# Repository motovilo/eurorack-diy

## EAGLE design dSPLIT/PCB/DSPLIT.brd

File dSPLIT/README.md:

# dSPLIT
 5-way digital splitter, x2, x4 divider module

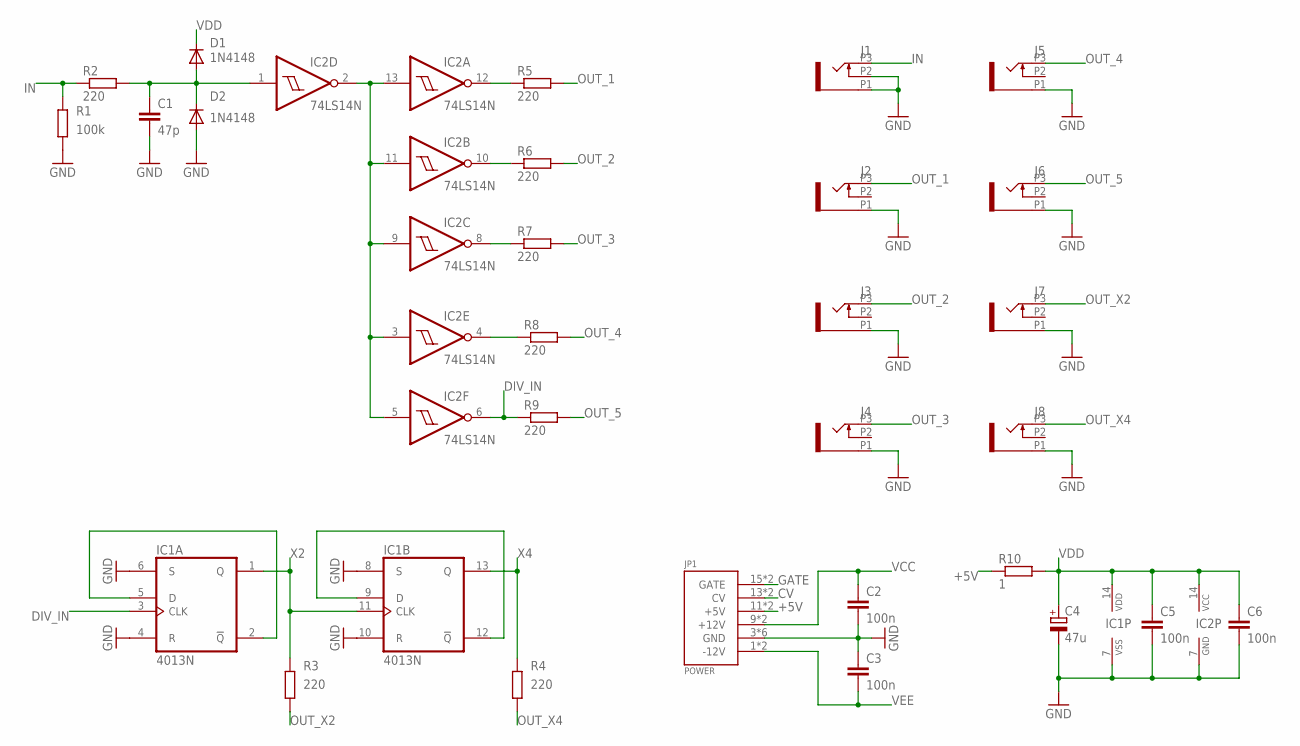
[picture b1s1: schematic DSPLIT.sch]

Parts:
C1: 47p; C050-024X044
C2, C3, C5, C6: 100n; C050-024X044
C4: 47u; E2,5-6
D1, D2: 1N4148; DO35-7
IC1: 4013N; DIL14
IC2: 74LS14N; DIL14
J1, J2, J3, J4, J5, J6, J7, J8: WQP-PJ302M_JACK
JP1: POWER; POWER_16
R1: 100k; 0204/7
R2, R3, R4, R5, R6, R7, R8, R9: 220; 0204/7
R10: 1; 0204/7

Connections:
+5V: JP1.11 (+5V), JP1.12 (+5V), R10.1
CV: JP1.13 (CV), JP1.14 (CV)
DIV_IN: IC1.3 (CLK), IC2.6 (O), R9.1
GATE: JP1.15 (GATE), JP1.16 (GATE)
GND: C1.2, C2.2, C3.1, C4.-, C5.2, C6.2, D2.A, IC1.4 (R), IC1.6 (S), IC1.7 (VSS), IC1.8 (S), IC1.10 (R), IC2.7 (GND), J1.P1 (1), J1.P2 (2), J2.P1 (1), J3.P1 (1), J4.P1 (1), J5.P1 (1), J6.P1 (1), J7.P1 (1), J8.P1 (1), JP1.3 (GND), JP1.4 (GND), JP1.5 (GND), JP1.6 (GND), JP1.7 (GND), JP1.8 (GND), R1.1
IN: J1.P3 (3), R1.2, R2.1
IN_1_: C1.1, D1.A, D2.C, IC2.1 (I), R2.2
unnamed: IC1.2 (!Q), IC1.5 (D)
unnamed: IC2.2 (O), IC2.3 (I), IC2.5 (I), IC2.9 (I), IC2.11 (I), IC2.13 (I)
unnamed: IC1.9 (D), IC1.12 (!Q)
unnamed: IC2.12 (O), R5.1
unnamed: IC2.10 (O), R6.1
unnamed: IC2.8 (O), R7.1
unnamed: IC2.4 (O), R8.1
OUT_1: J2.P3 (3), R5.2
OUT_2: J3.P3 (3), R6.2
OUT_3: J4.P3 (3), R7.2
OUT_4: J5.P3 (3), R8.2
OUT_5: J6.P3 (3), R9.2
OUT_X2: J7.P3 (3), R3.2
OUT_X4: J8.P3 (3), R4.2
VCC: C2.1, JP1.9 (+12V), JP1.10 (+12V)
VDD: C4.+, C5.1, C6.1, D1.C, IC1.14 (VDD), IC2.14 (VCC), R10.2
VEE: C3.2, JP1.1 (-12V), JP1.2 (-12V)
X2: IC1.1 (Q), IC1.11 (CLK), R3.1
X4: IC1.13 (Q), R4.1

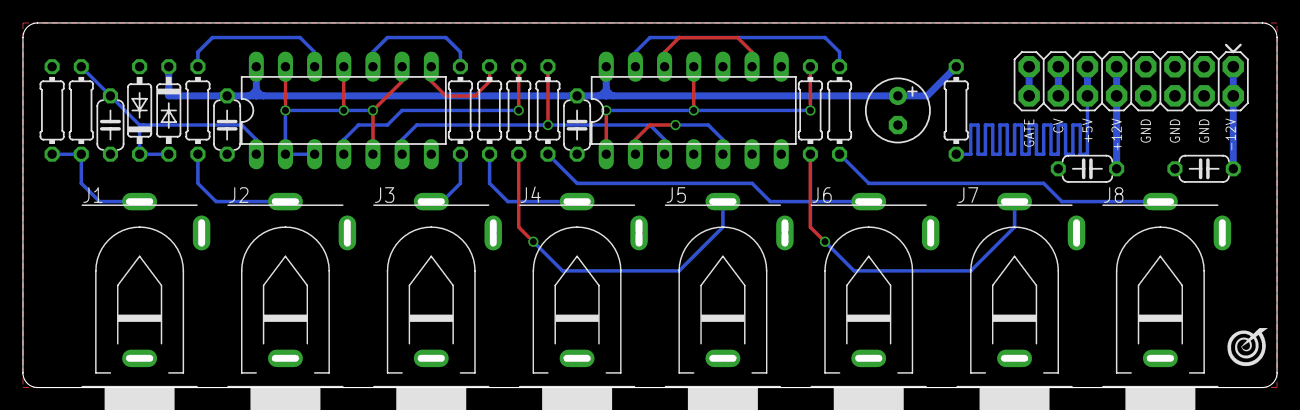
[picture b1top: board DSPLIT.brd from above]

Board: 2 copper layers, 108.6 x 31.1 mm, 31 parts (1 on the bottom side), 26 nets.

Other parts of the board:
U$1: LOGO_SPACE_002
U$2: LOGO_1

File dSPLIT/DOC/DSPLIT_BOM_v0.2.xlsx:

Part | QTY | Value | Device | Package
C1 | 1 | 47p | CAPACITOR CERAMIC | C050-024X044
C2, C3, C5, C6 | 4 | 100n | CAPACITOR CERAMIC | C050-024X044
C4 | 1 | 47u | CAPACITOR ELECTROLYTIC | E2,5-6
D1, D2 | 2 | 1N4148 | DIODE | DO35-7
IC1 | 1 | CD4013N | Dual D FLIP FLOP, set/reset | DIL14
IC2 | 1 | 74LS14N (or CD40106) | Hex schmitt trigger INVERTER | DIL14
J1, J2, J3, J4, J5, J6, J7, J8 | 8 | WQP-PJ302M | MONO JACK 3.5mm with switch angle mount | WQP-PJ302M_JACK
JP1 | 1 | POWER | PIN HEADER 16*2 PITCH=2.54mm | PLD-16 (DS1021-2x8)
R1 | 1 | 100k | RESISTOR METAL FILM 1/4W | 0204/7
R2, R3, R4, R5, R6, R7, R8, R9 | 8 | 220 | RESISTOR METAL FILM 1/4W | 0204/7
R10 | 1 | 1 | RESISTOR METAL FILM 1/4W | 0204/7
IC1, IC2 | 2 | IC SOCKET | IC SOCKET DIL 14 PIN | SCS-14 (DS1009-14AN)
Screw M3 | 2 |  | SCREW M3*6 ROUND CAP | M3*6
Flat Cable 10 PIN | 1 |  | Flat Cable 1.27mm*16 | DS1057-16-30 (FRC-16-30)
FC-16P Connector for flat cable | 2 | IDC-16F | 2.54mm IDC SOCKET 16 pin | IDC-16F (DS1016-16)
dSPLIT PCB v.0.2 | 1
dSPLIT PANEL | 1
NUTS for JACKS | 8

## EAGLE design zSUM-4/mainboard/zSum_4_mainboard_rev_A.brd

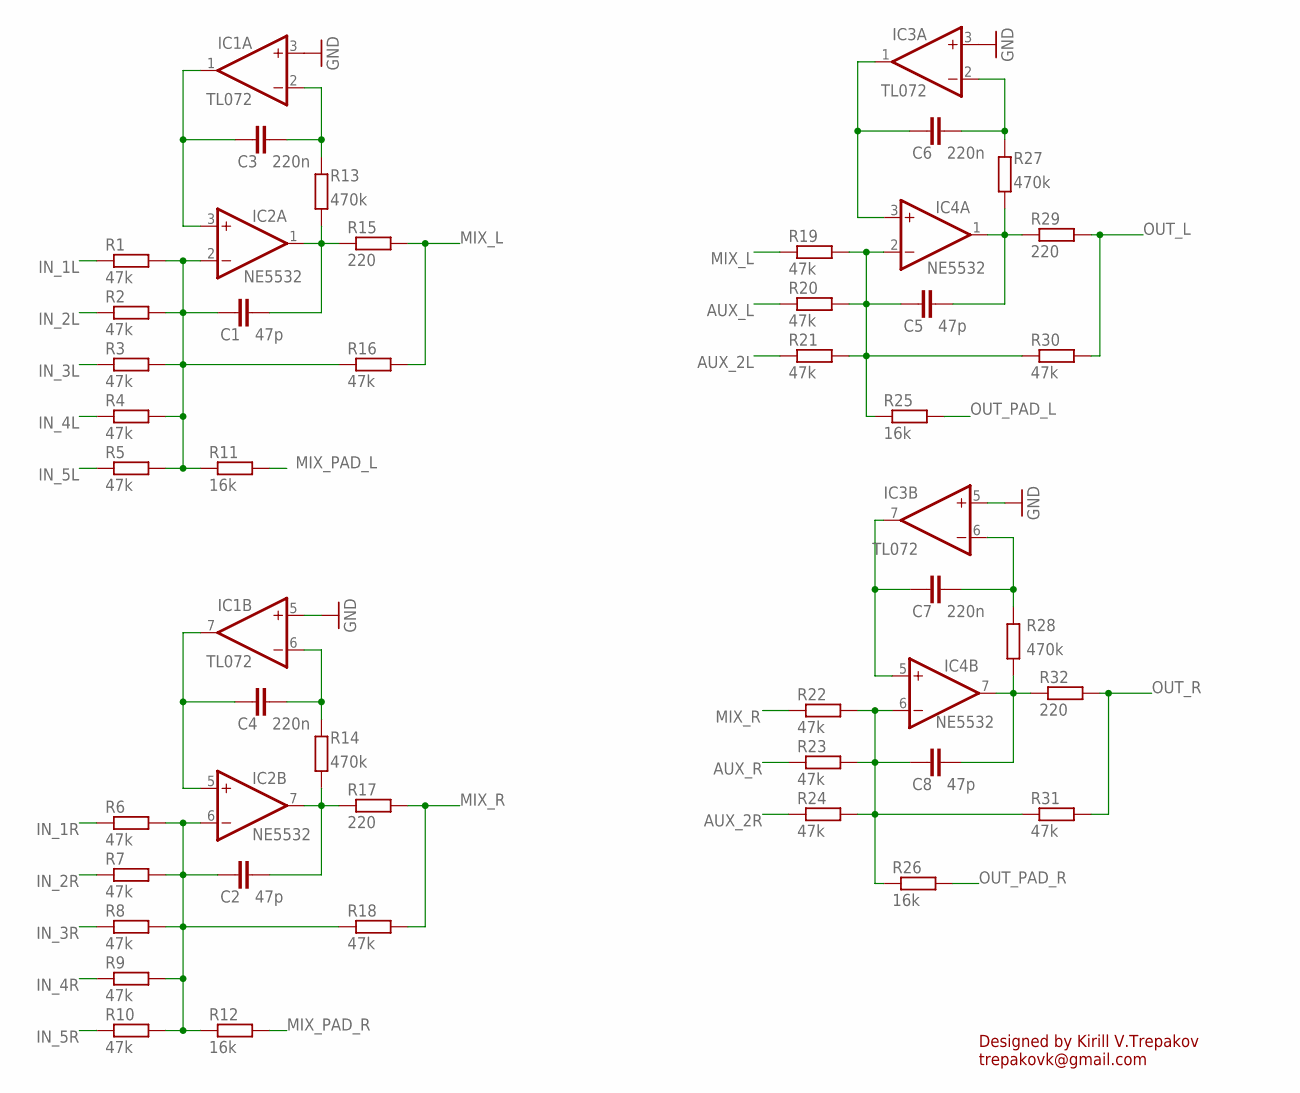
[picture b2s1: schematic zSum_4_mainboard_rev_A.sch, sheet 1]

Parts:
C1, C2, C5, C8: 47p; C025-025X050
C3, C4, C6, C7: 220n; C050-025X075
IC1, IC3: TL072; DIL08
IC2, IC4: NE5532; DIL08
R1, R2, R3, R4, R5, R6, R7, R8, R9, R10, R16, R18, R19, R20, R21, R22, R23, R24, R30, R31: 47k; 0207/7
R11, R12, R25, R26: 16k; 0207/7
R13, R14, R27, R28: 470k; 0207/7
R15, R17, R29, R32: 220; 0207/7

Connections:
AUX_2L: R21.1; also elsewhere on the board
AUX_2R: R24.1; also elsewhere on the board
AUX_L: R20.1; also elsewhere on the board
AUX_R: R23.1; also elsewhere on the board
BIAS_L: C3.2, IC1.1 (OUT), IC2.3 (+IN)
BIAS_L1: C6.2, IC3.1 (OUT), IC4.3 (+IN)
BIAS_R: C4.2, IC1.7 (OUT), IC2.5 (+IN)
BIAS_R1: C7.2, IC3.7 (OUT), IC4.5 (+IN)
GND: IC1.3 (+IN), IC1.5 (+IN), IC3.3 (+IN), IC3.5 (+IN); also elsewhere on the board
IN_1L: R1.1; also elsewhere on the board
IN_1R: R6.1; also elsewhere on the board
IN_2L: R2.1; also elsewhere on the board
IN_2R: R7.1; also elsewhere on the board
IN_3L: R3.1; also elsewhere on the board
IN_3R: R8.1; also elsewhere on the board
IN_4L: R4.1; also elsewhere on the board
IN_4R: R9.1; also elsewhere on the board
IN_5L: R5.1; also elsewhere on the board
IN_5R: R10.1; also elsewhere on the board
MIX_L: R15.2, R16.2, R19.1; also elsewhere on the board
MIX_PAD_L: R11.2; also elsewhere on the board
MIX_PAD_R: R12.2; also elsewhere on the board
MIX_R: R17.2, R18.2, R22.1; also elsewhere on the board
unnamed: C6.1, IC3.2 (-IN), R27.1
unnamed: C7.1, IC3.6 (-IN), R28.1
unnamed: C3.1, IC1.2 (-IN), R13.1
unnamed: C1.1, IC2.1 (OUT), R13.2, R15.1
unnamed: C4.1, IC1.6 (-IN), R14.1
unnamed: C2.1, IC2.7 (OUT), R14.2, R17.1
unnamed: C5.1, IC4.1 (OUT), R27.2, R29.1
unnamed: C8.1, IC4.7 (OUT), R28.2, R32.1
OUT_L: R29.2, R30.2; also elsewhere on the board
OUT_PAD_L: R25.2; also elsewhere on the board
OUT_PAD_R: R26.2; also elsewhere on the board
OUT_R: R31.2, R32.2; also elsewhere on the board
VGND_MIX_L: C1.2, IC2.2 (-IN), R1.2, R2.2, R3.2, R4.2, R5.2, R11.1, R16.1
VGND_MIX_R: C2.2, IC2.6 (-IN), R6.2, R7.2, R8.2, R9.2, R10.2, R12.1, R18.1
VGND_OUT_L: C5.2, IC4.2 (-IN), R19.2, R20.2, R21.2, R25.1, R30.1
VGND_OUT_R: C8.2, IC4.6 (-IN), R22.2, R23.2, R24.2, R26.1, R31.1

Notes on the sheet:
Designed by Kirill V.Trepakov trepakovk@gmail.com

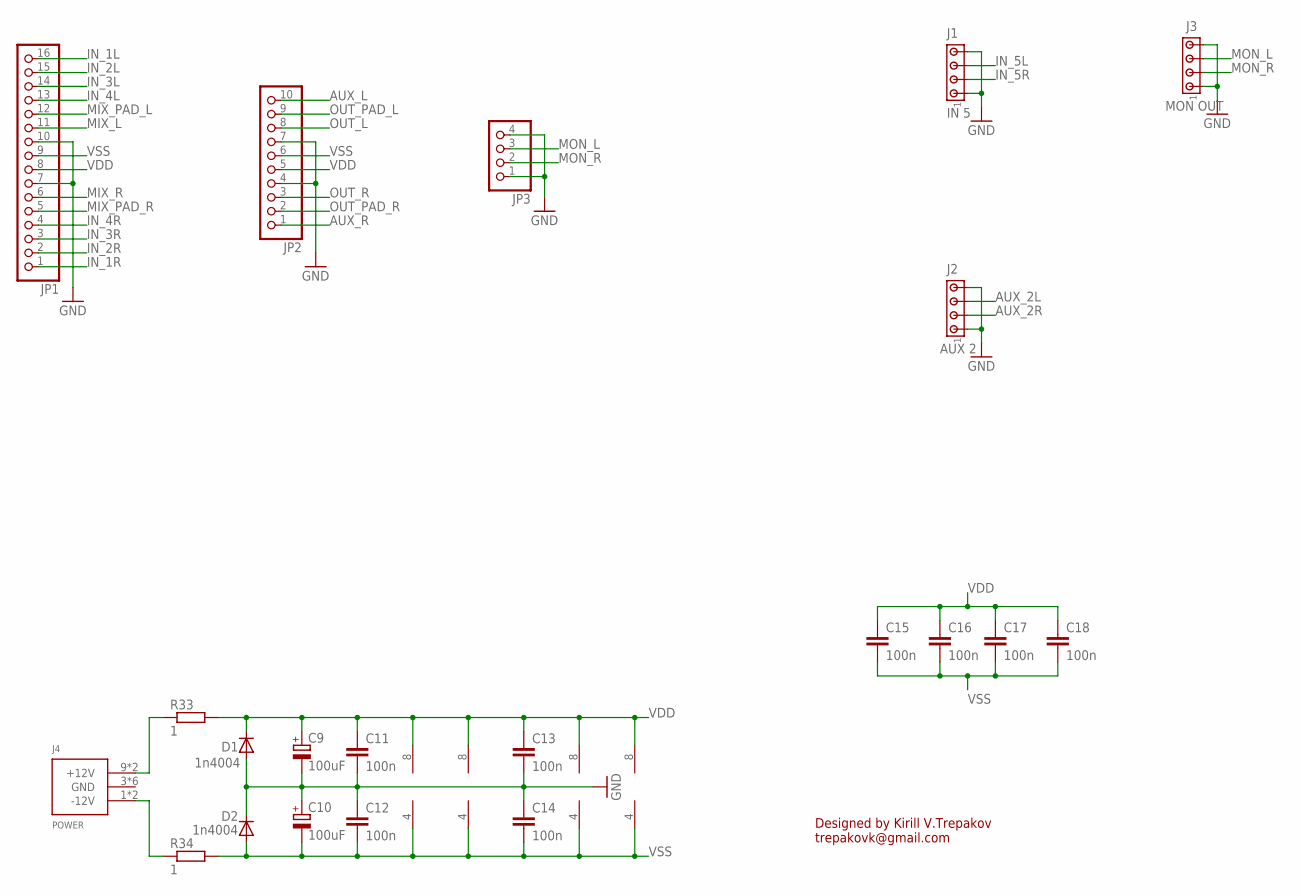
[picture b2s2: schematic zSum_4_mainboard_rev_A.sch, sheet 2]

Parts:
C9, C10: 100uF; E2,5-6
C11, C12, C13, C14: 100n; C050-025X075
C15, C16, C17, C18: 100n; C1206
D1, D2: 1n4004; DO41-7.6
IC1, IC3: TL072; DIL08
IC2, IC4: NE5532; DIL08
J1: IN 5; 10X04MTA
J2: AUX 2; 10X04MTA
J3: MON OUT; 10X04MTA
J4: POWER; POWER_10M
JP1: PINHD-1X16; 1X16_
JP2: PINHD-1X10; 1X10_
JP3: PINHD-1X4; 1X04
R33, R34: 1; 0207/7

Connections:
AUX_2L: J2.3; also elsewhere on the board
AUX_2R: J2.2; also elsewhere on the board
AUX_L: JP2.10; also elsewhere on the board
AUX_R: JP2.1; also elsewhere on the board
GND: C9.-, C10.+, C11.2, C12.1, C13.2, C14.1, D1.A, D2.C, J1.1, J1.4, J2.1, J2.4, J3.1, J3.4, JP1.7, JP1.10, JP2.4, JP2.7, JP3.1, JP3.4; also elsewhere on the board
IN_1L: JP1.16; also elsewhere on the board
IN_1R: JP1.1; also elsewhere on the board
IN_2L: JP1.15; also elsewhere on the board
IN_2R: JP1.2; also elsewhere on the board
IN_3L: JP1.14; also elsewhere on the board
IN_3R: JP1.3; also elsewhere on the board
IN_4L: JP1.13; also elsewhere on the board
IN_4R: JP1.4; also elsewhere on the board
IN_5L: J1.3; also elsewhere on the board
IN_5R: J1.2; also elsewhere on the board
MIX_L: JP1.11; also elsewhere on the board
MIX_PAD_L: JP1.12; also elsewhere on the board
MIX_PAD_R: JP1.5; also elsewhere on the board
MIX_R: JP1.6; also elsewhere on the board
MON_L: J3.3, JP3.3
MON_R: J3.2, JP3.2
unnamed: J4.1 (-12V), J4.2 (-12V), R34.1
unnamed: J4.9 (+12V), J4.10 (+12V), R33.1
OUT_L: JP2.8; also elsewhere on the board
OUT_PAD_L: JP2.9; also elsewhere on the board
OUT_PAD_R: JP2.2; also elsewhere on the board
OUT_R: JP2.3; also elsewhere on the board
VDD: C9.+, C11.1, C13.1, C15.1, C16.1, C17.1, C18.1, D1.C, IC1.8 (V+), IC2.8 (V+), IC3.8 (V+), IC4.8 (V+), JP1.8, JP2.5, R33.2
VSS: C10.-, C12.2, C14.2, C15.2, C16.2, C17.2, C18.2, D2.A, IC1.4 (V-), IC2.4 (V-), IC3.4 (V-), IC4.4 (V-), JP1.9, JP2.6, R34.2

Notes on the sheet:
Designed by Kirill V.Trepakov trepakovk@gmail.com

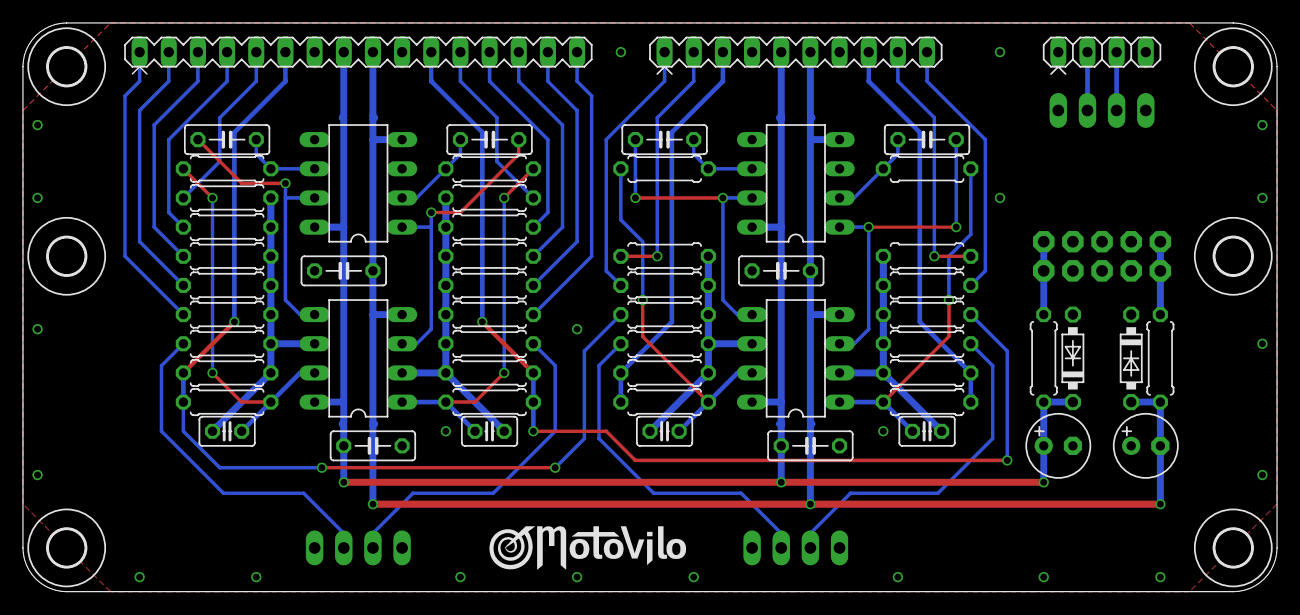
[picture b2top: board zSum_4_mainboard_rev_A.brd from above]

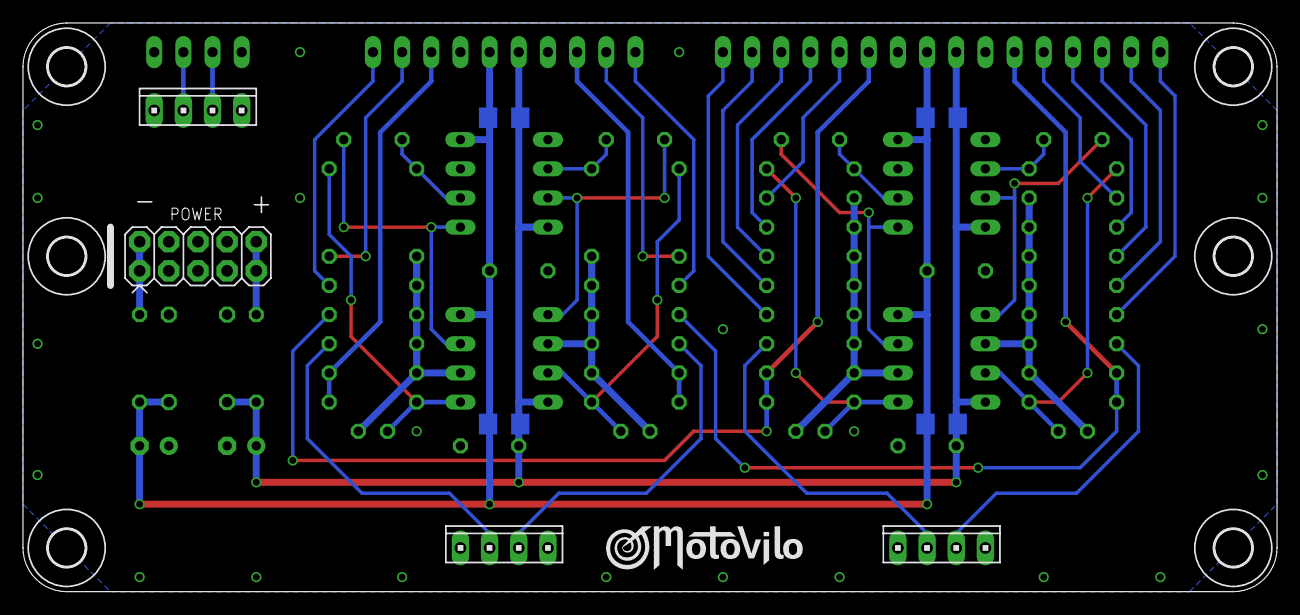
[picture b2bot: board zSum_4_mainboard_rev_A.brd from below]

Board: 2 copper layers, 109.2 x 49.5 mm, 73 parts (9 on the bottom side), 45 nets.

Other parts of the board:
U$1, U$2, U$3, U$4, U$5, U$6: 3,2_NEW
U$7, U$8: LOGO_SPACE_002

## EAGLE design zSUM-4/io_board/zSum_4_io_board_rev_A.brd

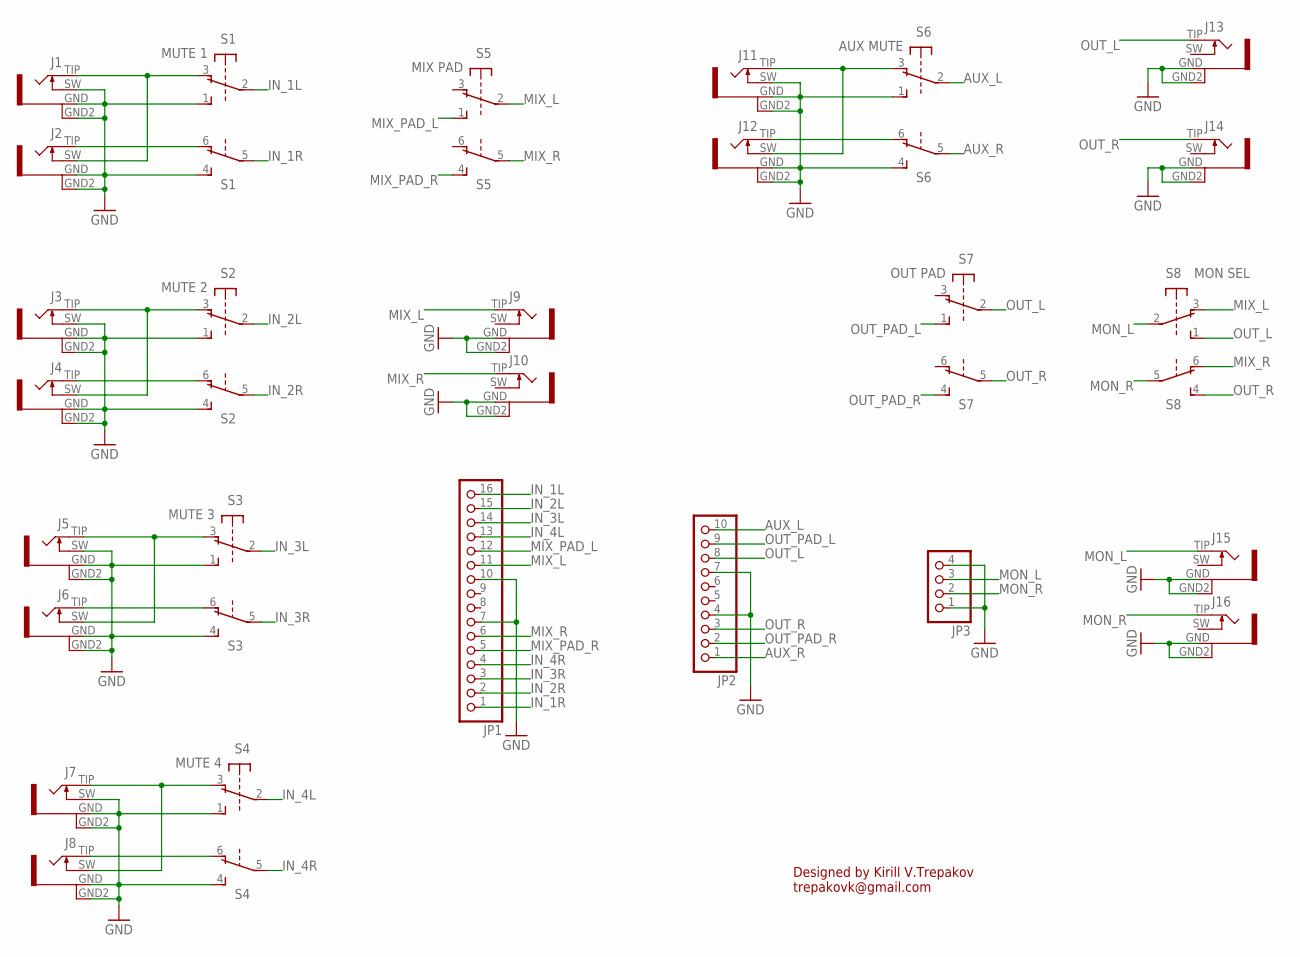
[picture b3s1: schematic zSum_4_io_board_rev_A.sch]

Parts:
J1, J2, J3, J4, J5, J6, J7, J8, J9, J10, J11, J12, J13, J14, J15, J16: PJ301WQP; WQP_PJ_301BM
JP1: PINHD-1X16; 1X16_
JP2: PINHD-1X10; 1X10_
JP3: PINHD-1X4; 1X04
S1: MUTE 1; 9077-2
S2: MUTE 2; 9077-2
S3: MUTE 3; 9077-2
S4: MUTE 4; 9077-2
S5: MIX PAD; 9077-2
S6: AUX MUTE; 9077-2
S7: OUT PAD; 9077-2
S8: MON SEL; 9077-2

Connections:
AUX_L: JP2.10, S6.2
AUX_R: JP2.1, S6.5
GND: J1.GND (1), J1.GND2 (4), J1.SW (3), J2.GND (1), J2.GND2 (4), J3.GND (1), J3.GND2 (4), J3.SW (3), J4.GND (1), J4.GND2 (4), J5.GND (1), J5.GND2 (4), J5.SW (3), J6.GND (1), J6.GND2 (4), J7.GND (1), J7.GND2 (4), J7.SW (3), J8.GND (1), J8.GND2 (4), J9.GND (1), J9.GND2 (4), J10.GND (1), J10.GND2 (4), J11.GND (1), J11.GND2 (4), J11.SW (3), J12.GND (1), J12.GND2 (4), J13.GND (1), J13.GND2 (4), J14.GND (1), J14.GND2 (4), J15.GND (1), J15.GND2 (4), J16.GND (1), J16.GND2 (4), JP1.7, JP1.10, JP2.4, JP2.7, JP3.1, JP3.4, S1.1 (S), S1.4 (S), S2.1 (S), S2.4 (S), S3.1 (S), S3.4 (S), S4.1 (S), S4.4 (S), S6.1 (S), S6.4 (S)
IN_1L: JP1.16, S1.2
IN_1R: JP1.1, S1.5
IN_2L: JP1.15, S2.2
IN_2R: JP1.2, S2.5
IN_3L: JP1.14, S3.2
IN_3R: JP1.3, S3.5
IN_4L: JP1.13, S4.2
IN_4R: JP1.4, S4.5
MIX_L: J9.TIP (2), JP1.11, S5.2, S8.3 (O)
MIX_PAD_L: JP1.12, S5.1 (S)
MIX_PAD_R: JP1.5, S5.4 (S)
MIX_R: J10.TIP (2), JP1.6, S5.5, S8.6 (O)
MON_L: J15.TIP (2), JP3.3, S8.2
MON_R: J16.TIP (2), JP3.2, S8.5
unnamed: J1.TIP (2), J2.SW (3), S1.3 (O)
unnamed: J3.TIP (2), J4.SW (3), S2.3 (O)
unnamed: J2.TIP (2), S1.6 (O)
unnamed: J4.TIP (2), S2.6 (O)
unnamed: J5.TIP (2), J6.SW (3), S3.3 (O)
unnamed: J6.TIP (2), S3.6 (O)
unnamed: J7.TIP (2), J8.SW (3), S4.3 (O)
unnamed: J8.TIP (2), S4.6 (O)
unnamed: J11.TIP (2), J12.SW (3), S6.3 (O)
unnamed: J12.TIP (2), S6.6 (O)
OUT_L: J13.TIP (2), JP2.8, S7.2, S8.1 (S)
OUT_PAD_L: JP2.9, S7.1 (S)
OUT_PAD_R: JP2.2, S7.4 (S)
OUT_R: J14.TIP (2), JP2.3, S7.5, S8.4 (S)

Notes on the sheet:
Designed by Kirill V.Trepakov trepakovk@gmail.com

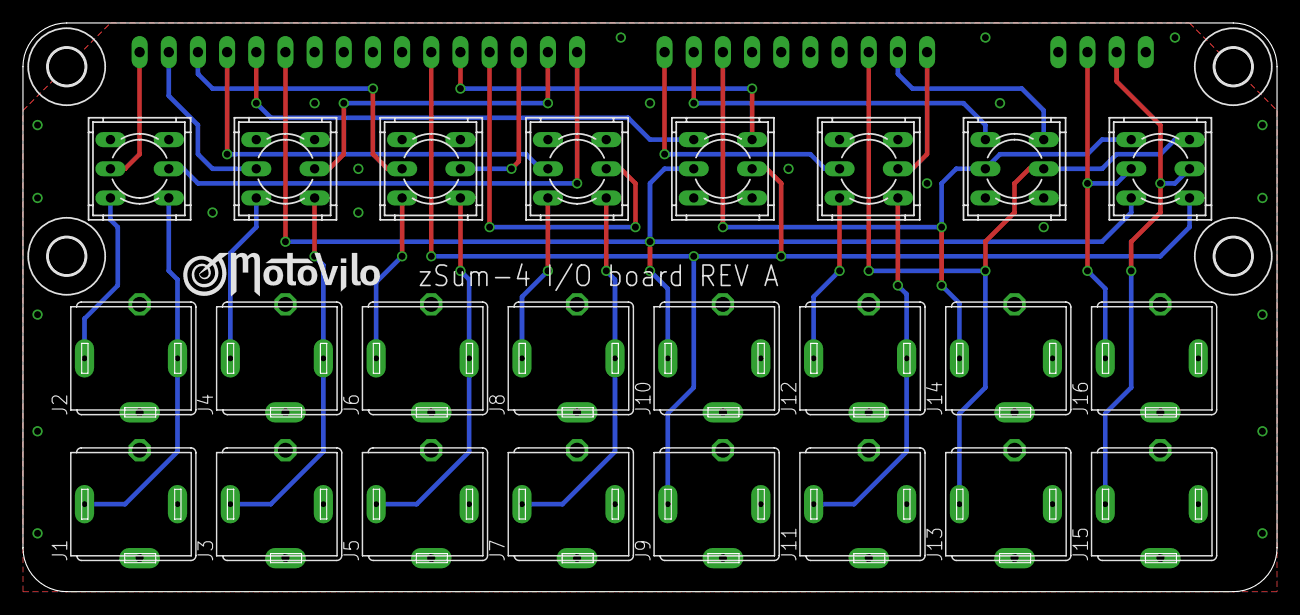
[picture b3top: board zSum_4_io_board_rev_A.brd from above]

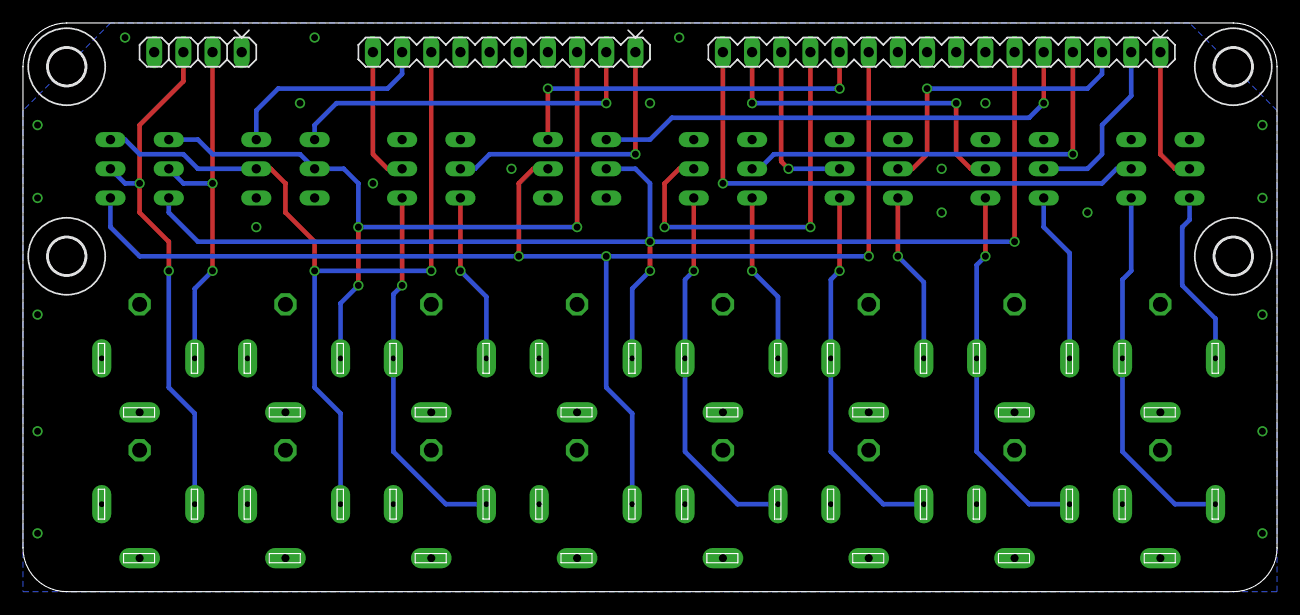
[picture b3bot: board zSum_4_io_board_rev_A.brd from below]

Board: 2 copper layers, 109.2 x 49.5 mm, 32 parts (3 on the bottom side), 31 nets.

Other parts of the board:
U$1, U$2, U$3, U$4: 3,2_NEW
U$6: LOGO_SPACE_002

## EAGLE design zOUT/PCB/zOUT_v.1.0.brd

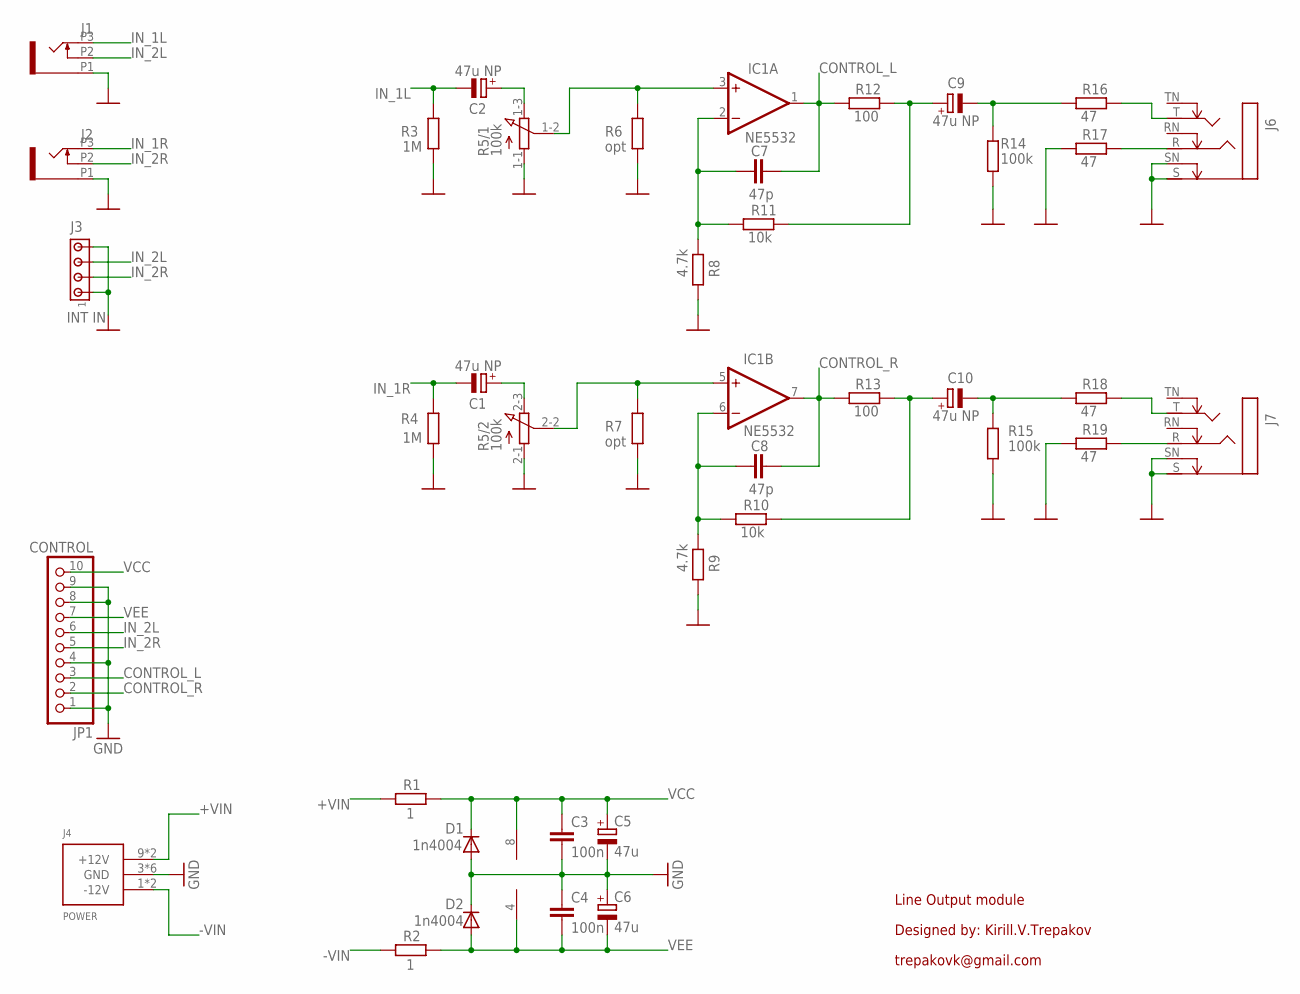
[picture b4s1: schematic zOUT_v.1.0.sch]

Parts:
C1, C2, C9, C10: 47u NP; E2,5-6
C3, C4: 100n; C050-024X044
C5, C6: 47u; E2,5-5
C7, C8: 47p; C050-024X044
D1, D2: 1n4004; DO41-7.6
IC1: NE5532; DIL08
J1: IN L; WQP-PJ302M_JACK
J2: IN R; WQP-PJ302M_JACK
J3: INT IN; 10X04MTA
J4: POWER; POWER_10
J6: OUT L; NMJ6HC-S
J7: OUT R; NMJ6HC-S
JP1: CONTROL; 1X10
R1, R2: 1; 0204/7
R3, R4: 1M; 0204/7
R5: 100k; 3RP/1610G
R6, R7: opt; 0204/7
R8, R9: 4.7k; 0204/7
R10, R11: 10k; 0204/7
R12, R13: 100; 0204/7
R14, R15: 100k; 0204/7
R16, R17, R18, R19: 47; 0204/7

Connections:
+VIN: J4.9 (+12V), J4.10 (+12V), R1.1
-VIN: J4.1 (-12V), J4.2 (-12V), R2.1
CONTROL_L: C7.2, IC1.1 (OUT), JP1.3, R12.1
CONTROL_R: C8.2, IC1.7 (OUT), JP1.2, R13.1
GND: C3.2, C4.1, C5.-, C6.+, D1.A, D2.C, J1.P1 (1), J2.P1 (1), J3.1, J3.4, J4.3 (GND), J4.4 (GND), J4.5 (GND), J4.6 (GND), J4.7 (GND), J4.8 (GND), J6.S, J6.SN, J7.S, J7.SN, JP1.1, JP1.4, JP1.8, JP1.9, R3.2, R4.2, R5.1-1 (A), R5.2-1 (A), R6.2, R7.2, R8.2, R9.2, R14.2, R15.2, R17.1, R19.1
IN_1L: C2.-, J1.P3 (3), R3.1
IN_1R: C1.-, J2.P3 (3), R4.1
IN_2L: J1.P2 (2), J3.3, JP1.6
IN_2R: J2.P2 (2), J3.2, JP1.5
unnamed: C10.+, R10.2, R13.2
unnamed: J6.R, R17.2
unnamed: C9.+, R11.2, R12.2
unnamed: J7.R, R19.2
unnamed: J6.T, R16.2
unnamed: C1.+, R5.2-3 (E)
unnamed: J7.T, R18.2
unnamed: C9.-, R14.1, R16.1
unnamed: C8.1, IC1.6 (-IN), R9.1, R10.1
unnamed: C2.+, R5.1-3 (E)
unnamed: IC1.3 (+IN), R5.1-2 (S), R6.1
unnamed: IC1.5 (+IN), R5.2-2 (S), R7.1
unnamed: C10.-, R15.1, R18.1
VCC: C3.1, C5.+, D1.C, IC1.8 (V+), JP1.10, R1.2
VEE: C4.2, C6.-, D2.A, IC1.4 (V-), JP1.7, R2.2
VGND_L: C7.1, IC1.2 (-IN), R8.1, R11.1

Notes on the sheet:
trepakovk@gmail.com
Line Output module
Designed by: Kirill.V.Trepakov

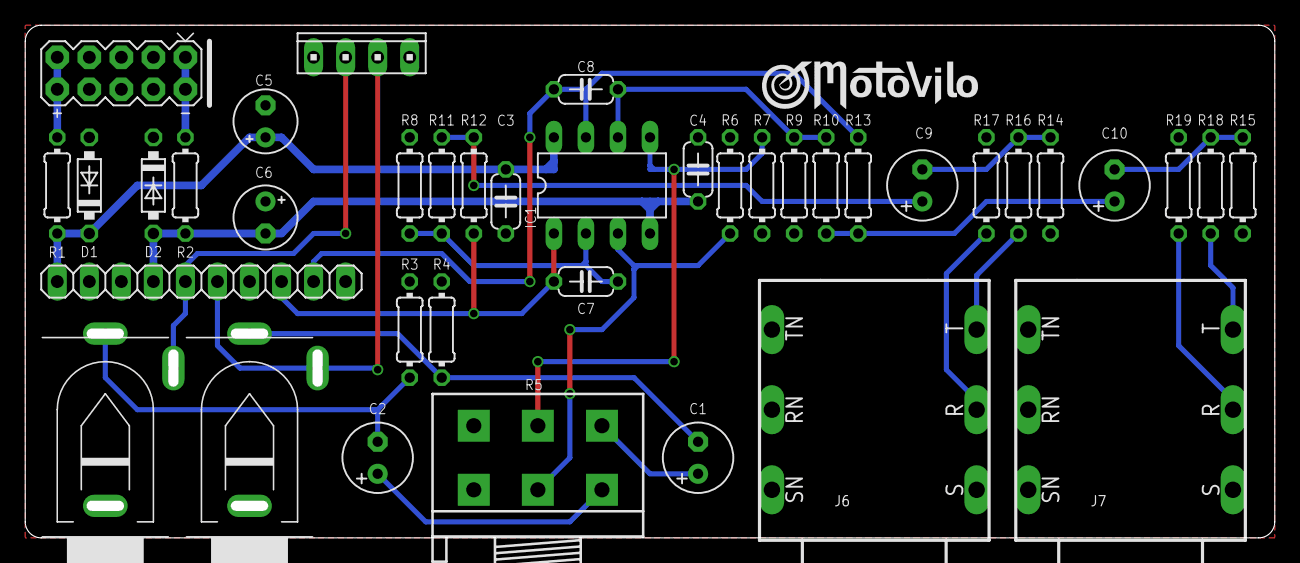
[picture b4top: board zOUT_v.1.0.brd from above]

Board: 2 copper layers, 98.2 x 39.8 mm, 40 parts (0 on the bottom side), 25 nets.

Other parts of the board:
U$2: LOGO_SPACE_002

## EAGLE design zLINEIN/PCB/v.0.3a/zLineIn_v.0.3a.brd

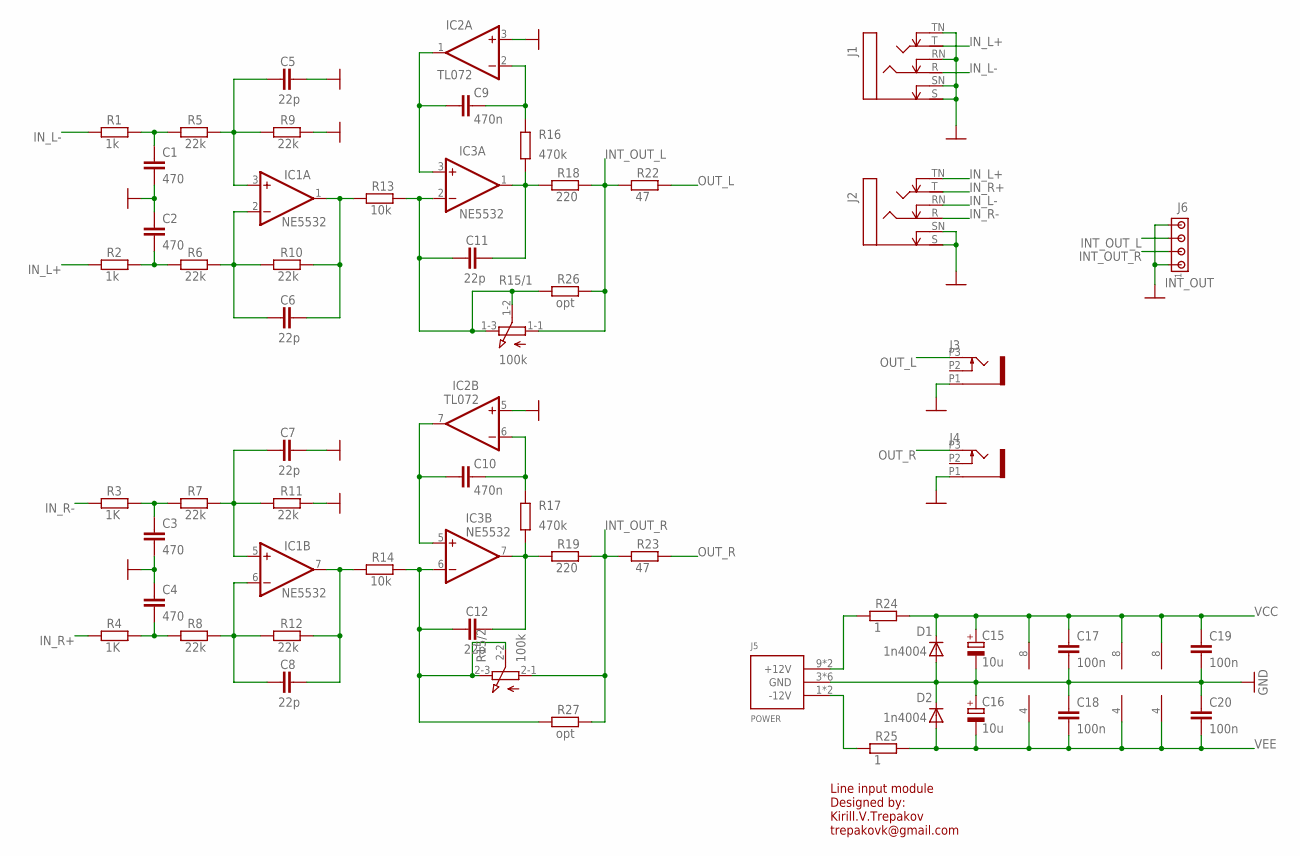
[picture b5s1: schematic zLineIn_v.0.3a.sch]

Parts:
C1, C2, C3, C4: 470; C050-024X044
C5, C6, C7, C8, C11, C12: 22p; C050-024X044
C9, C10: 470n; C075-032X103
C15, C16: 10u; E2,5-5
C17, C18, C19, C20: 100n; C050-024X044
D1, D2: 1n4004; DO41-7.6
IC1, IC3: NE5532; DIL08_
IC2: TL072; DIL08_
J1: IN_L; NMJ6HC-S
J2: IN_R; NMJ6HC-S
J3, J4: WQP-PJ302M_JACK
J5: POWER; POWER_10
J6: INT_OUT; 10X04MTA
R1, R2: 1k; 0204/7
R3, R4: 1K; 0204/7
R5, R6, R7, R8, R9, R10, R11, R12: 22k; 0204/7
R13, R14: 10k; 0204/7
R15: 100k; 3RP/1610G
R16, R17: 470k; 0204/7
R18, R19: 220; 0204/7
R22, R23: 47; 0204/7
R24, R25: 1; 0204/7
R26, R27: opt; 0204/7

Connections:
CTRL_L_OUT: C11.2, IC3.1 (OUT), R16.2, R18.1
CTRL_R_OUT: C12.2, IC3.7 (OUT), R17.2, R19.1
GND: C1.2, C2.1, C3.2, C4.1, C5.2, C7.2, C15.-, C16.+, C17.2, C18.1, C19.2, C20.1, D1.A, D2.C, IC2.3 (+IN), IC2.5 (+IN), J1.RN, J1.S, J1.SN, J1.TN, J2.S, J2.SN, J3.P1 (1), J4.P1 (1), J5.3 (GND), J5.4 (GND), J5.5 (GND), J5.6 (GND), J5.7 (GND), J5.8 (GND), J6.1, J6.4, R9.2, R11.2
INT_OUT_L: J6.3, R15.1-1 (1), R18.2, R22.1, R26.2
INT_OUT_R: J6.2, R15.2-1 (1), R19.2, R23.1, R27.2
IN_L+: J1.T, J2.TN, R2.1
IN_L-: J1.R, J2.RN, R1.1
IN_R+: J2.T, R4.1
IN_R-: J2.R, R3.1
unnamed: J5.9 (+12V), J5.10 (+12V), R24.1
unnamed: C9.2, IC2.2 (-IN), R16.1
unnamed: C10.2, IC2.6 (-IN), R17.1
unnamed: J5.1 (-12V), J5.2 (-12V), R25.1
unnamed: C3.1, R3.2, R7.1
unnamed: C4.2, R4.2, R8.1
unnamed: C7.1, IC1.5 (+IN), R7.2, R11.1
unnamed: C1.1, R1.2, R5.1
unnamed: C2.2, R2.2, R6.1
unnamed: C5.1, IC1.3 (+IN), R5.2, R9.1
unnamed: C6.1, IC1.2 (-IN), R6.2, R10.1
unnamed: C8.1, IC1.6 (-IN), R8.2, R12.1
OFFSET_L: C9.1, IC2.1 (OUT), IC3.3 (+IN)
OFFSET_R: C10.1, IC2.7 (OUT), IC3.5 (+IN)
OUT_L: J3.P3 (3), R22.2
OUT_R: J4.P3 (3), R23.2
UNBAL_L: C6.2, IC1.1 (OUT), R10.2, R13.1
UNBAL_R: C8.2, IC1.7 (OUT), R12.2, R14.1
VCC: C15.+, C17.1, C19.1, D1.C, IC1.8 (V+), IC2.8 (V+), IC3.8 (V+), R24.2
VEE: C16.-, C18.2, C20.2, D2.A, IC1.4 (V-), IC2.4 (V-), IC3.4 (V-), R25.2
VGND_L: C11.1, IC3.2 (-IN), R13.2, R15.1-2 (2), R15.1-3 (3), R26.1
VGND_R: C12.1, IC3.6 (-IN), R14.2, R15.2-2 (2), R15.2-3 (3), R27.1

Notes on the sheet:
Line input module Designed by: Kirill.V.Trepakov trepakovk@gmail.com

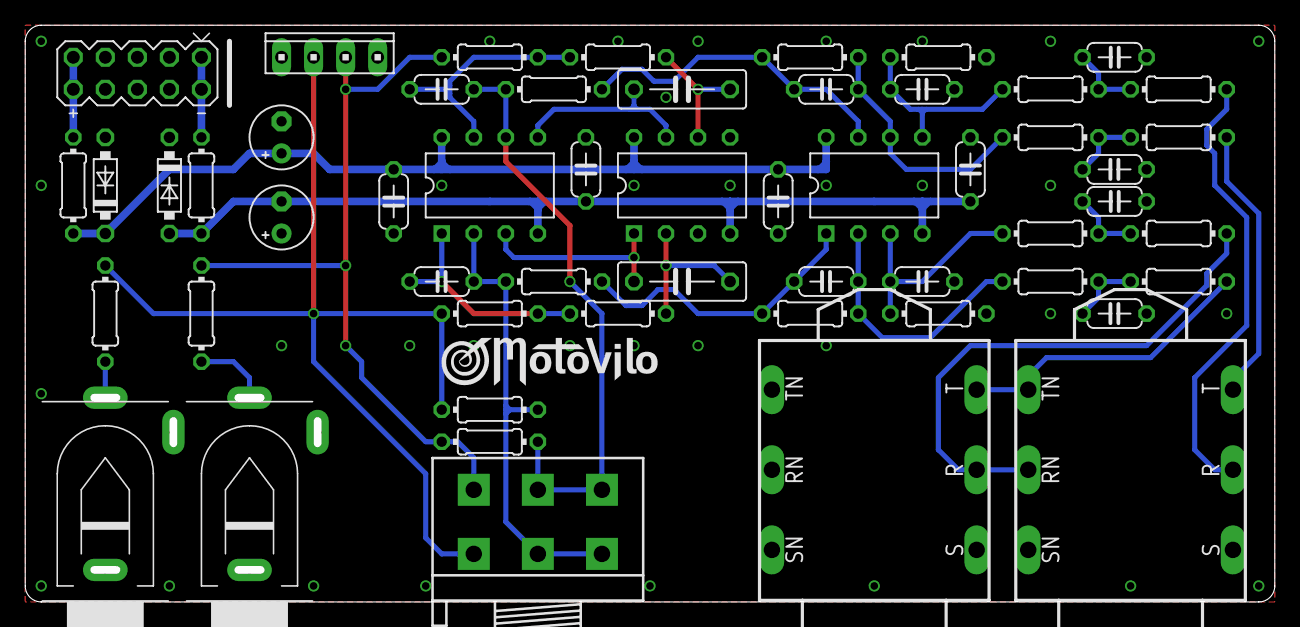
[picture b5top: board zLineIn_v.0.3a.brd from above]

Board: 2 copper layers, 98.5 x 45.1 mm, 55 parts (0 on the bottom side), 31 nets.

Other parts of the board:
U$2: LOGO_SPACE_002

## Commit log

2024-06-06 zLINEIN_added
2024-06-06 zOUT v.1.0 added
2024-06-06 zSUM-4 added
2024-06-06 zSUM-4 assembled photos added
2024-06-06 zLINEIN and zOUT photos added
2024-06-14 dSPLIT added
